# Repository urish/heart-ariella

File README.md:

# Heart-shaped Flashlight for Ariella

## Links

[A Practical Guide to Designing PCB Art](https://medium.com/@urish/a-practical-guide-to-designing-pcb-art-b5aa22926a5c) - A blog post explaining how I designed and manufactured the board

The project files are available either in [KiCad](kicad_leds/) or [Eagle](eagle/) format. The boards were manufactured by [OSH Park](https://oshpark.com).

## License

[CC-BY-SA](https://creativecommons.org/licenses/by-sa/4.0/)

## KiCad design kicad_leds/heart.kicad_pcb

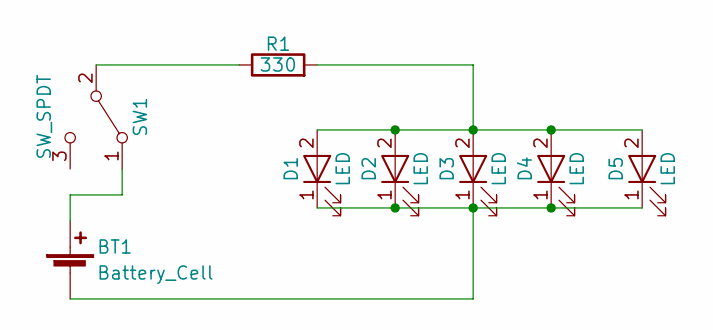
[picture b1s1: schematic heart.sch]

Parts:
BT1: Battery_Cell; BATCONN_12MM
D1, D2, D3, D4, D5: LED; LED_0603
R1: 330; R_0603_HandSoldering
SW1: SW_SPDT; AYZ0202

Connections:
unnamed: BT1.1 (+), SW1.1 (A)
unnamed: BT1.2 (-), D1.1 (K), D2.1 (K), D3.1 (K), D4.1 (K), D5.1 (K)
unnamed: D1.2 (A), D2.2 (A), D3.2 (A), D4.2 (A), D5.2 (A), R1.2
unnamed: R1.1, SW1.2 (B)

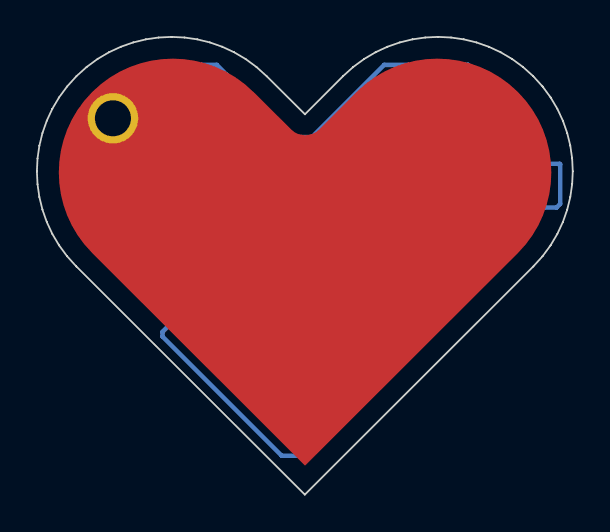
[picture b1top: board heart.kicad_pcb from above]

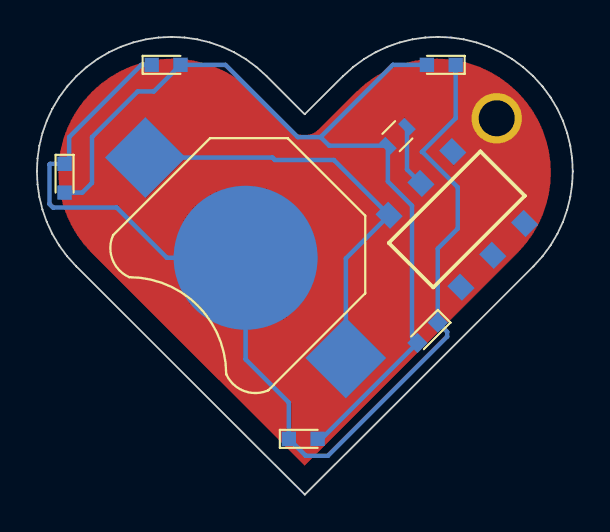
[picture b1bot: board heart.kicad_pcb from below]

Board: 2 copper layers, 29.8 x 25.4 mm, 9 parts (8 on the bottom side), 4 nets.

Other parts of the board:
svg2mod: G***; heart

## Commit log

2017-03-21 add heart photos
2017-08-18 move eagle files to `eagle` dir
2017-08-18 add heart shape SVG
2017-08-18 add kicad art files
2017-08-19 slightly modify inner heart shape
2017-08-19 set PCB gerber plot settings
2017-08-19 Restore original eagle files
2017-08-24 add kicad pcb with electronics
    5 leds + switch + battery holder
2017-09-02 Add links to README

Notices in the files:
parts and their libraries:
SparkFun-LED: Licensing: Creative Commons ShareAlike 4.0 International - https://creativecommons.org/licenses/by-sa/4.0
